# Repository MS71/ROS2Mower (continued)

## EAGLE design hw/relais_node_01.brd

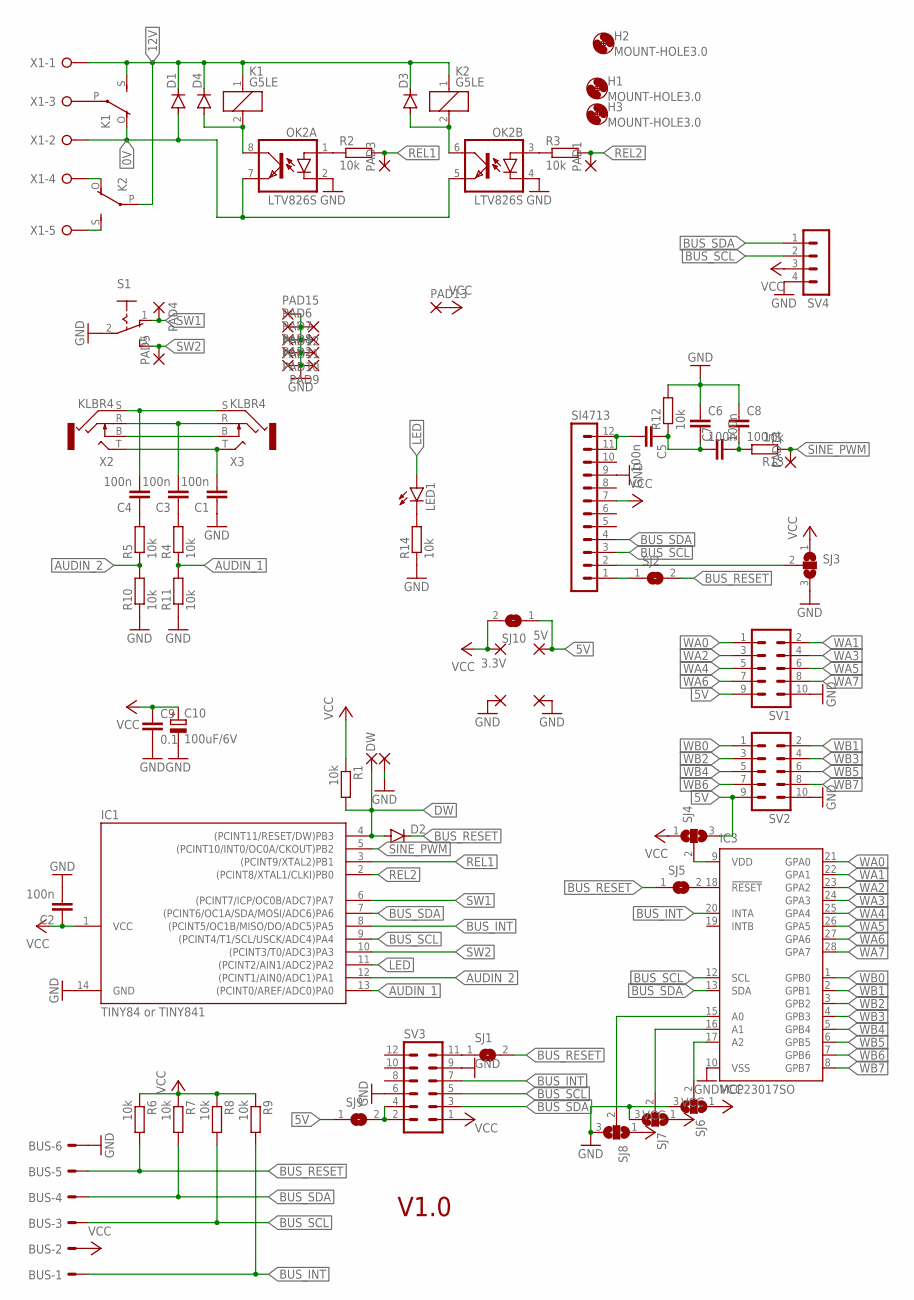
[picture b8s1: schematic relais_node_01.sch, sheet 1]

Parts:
3.3V, 5V: 1,6/0,8
BUS: ML6LE; ML6L
C1, C2, C3, C4, C5, C6, C7, C8: 100n; C0805
C9: 0.1; C0805
C10: 100uF/6V; B/3528-21R
D1: DIODE-MELF-MLL41; MELF-MLL41
D2, D3, D4: DIODE-MINIMELF; MINIMELF
DW: 1,6/0,9
GND_: 1,6/0,9
H1, H2, H3: MOUNT-HOLE3.0; 3,0
IC1: TINY84 or TINY841; SOIC14
IC3: MCP23017SO; SO28W
K1, K2: G5LE
LED1: LED3MM
OK2: LTV826S; DIL8-SMD
PAD1, PAD2, PAD3, PAD4, PAD5, PAD6, PAD7, PAD8, PAD9, PAD10, PAD11, PAD12, PAD13, PAD14, PAD15, PAD16, PAD17: 1,6/0,8
R1, R2, R3, R4, R5, R6, R7, R8, R9, R10, R11, R12, R13, R14: 10k; M0805
S1: 255SB
SI4713: MA12-1
SJ1, SJ2, SJ5, SJ9, SJ10: SJ
SJ3, SJ4, SJ6, SJ7, SJ8: SJ2W; SJ_2
SV1, SV2: ML10
SV3: MA06-2
SV4: MA04-1
X1: W237-05P; W237-5P
X2, X3: KLBR4

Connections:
0V: D1.A, K1.O, OK2.5 (EMIT), OK2.7 (EMIT), X1.2
5V: 5V.1, SJ4.3, SJ9.1, SJ10.1, SV1.9, SV2.9
5VRPI: SJ9.2, SV3.2, SV3.4
12V: D1.C, D3.C, D4.C, K1.1, K1.S, K2.1, K2.P, X1.1
AUDIN_1: IC1.13 ((PCINT0/AREF/ADC0)PA0), R4.1, R11.2
AUDIN_2: IC1.12 ((PCINT1/AIN0/ADC1)PA1), R5.1, R10.2
B: X2.B, X3.B
BUS_INT: BUS.1, IC1.8 ((PCINT5/OC1B/MISO/DO/ADC5)PA5), IC3.20 (INTA), R9.2, SV3.7
BUS_RESET: BUS.5, D2.C, R6.2, SJ1.2, SJ2.2, SJ5.1
BUS_SCL: BUS.3, IC1.9 ((PCINT4/T1/SCL/USCK/ADC4)PA4), IC3.12 (SCL), R8.2, SI4713.3, SV3.5, SV4.2
BUS_SDA: BUS.4, IC1.7 ((PCINT6/OC1A/SDA/MOSI/ADC6)PA6), IC3.13 (SDA), R7.2, SI4713.4, SV3.3, SV4.1
DW: D2.A, DW.1, IC1.4 ((PCINT11/RESET/DW)PB3), R1.2
GND: BUS.6, C1.1, C2.2, C6.1, C8.1, C9.2, C10.-, GND_.1, IC1.14 (GND), IC3.10 (VSS), OK2.2 (C), OK2.4 (C), PAD2.1, PAD6.1, PAD7.1, PAD8.1, PAD9.1, PAD10.1, PAD11.1, PAD12.1, PAD15.1, PAD16.1, PAD17.1, R10.1, R11.1, R12.2, R14.1, S1.2, SI4713.9, SJ3.3, SJ6.3, SJ7.3, SJ8.3, SV1.10, SV2.10, SV3.6, SV3.9, SV4.4
LED: IC1.11 ((PCINT2/AIN1/ADC2)PA2), LED1.A
unnamed: SJ1.1, SV3.11
unnamed: K1.P, X1.3
unnamed: D4.A, K1.2, OK2.8 (COL)
unnamed: D3.A, K2.2, OK2.6 (COL)
unnamed: K2.S, X1.5
unnamed: K2.O, X1.4
unnamed: OK2.1 (A), R2.1
unnamed: OK2.3 (A), R3.1
unnamed: C3.1, R4.2
unnamed: C4.1, R5.2
unnamed: SI4713.1, SJ2.1
unnamed: SI4713.2, SJ3.2
unnamed: LED1.K (C), R14.2
unnamed: IC3.9 (VDD), SJ4.2
unnamed: IC3.18 (!RESET), SJ5.2
unnamed: C5.2, SI4713.11, SI4713.12
unnamed: C5.1, C6.2, C7.1, R12.1
unnamed: C7.2, C8.2, R13.2
unnamed: IC3.17 (A2), SJ6.2
unnamed: IC3.16 (A1), SJ7.2
unnamed: IC3.15 (A0), SJ8.2
R: C3.2, X2.R, X3.R
REL1: IC1.3 ((PCINT9/XTAL2)PB1), PAD3.1, R2.2
REL2: IC1.2 ((PCINT8/XTAL1/CLKI)PB0), PAD1.1, R3.2
S: C4.2, X2.S, X3.S
SINE_PWM: IC1.5 ((PCINT10/INT0/OC0A/CKOUT)PB2), PAD14.1, R13.1
SW1: IC1.6 ((PCINT7/ICP/OC0B/ADC7)PA7), PAD4.1, S1.1 (O)
SW2: IC1.10 ((PCINT3/T0/ADC3)PA3), PAD5.1, S1.3 (S)
T: C1.2, X2.T, X3.T
VCC: 3.3V.1, BUS.2, C2.1, C9.1, C10.+, IC1.1 (VCC), PAD13.1, R1.1, R6.1, R7.1, R8.1, R9.1, SI4713.7, SJ3.1, SJ4.1, SJ6.1, SJ7.1, SJ8.1, SJ10.2, SV3.1, SV4.3
WA0: IC3.21 (GPA0), SV1.1
WA1: IC3.22 (GPA1), SV1.2
WA2: IC3.23 (GPA2), SV1.3
WA3: IC3.24 (GPA3), SV1.4
WA4: IC3.25 (GPA4), SV1.5
WA5: IC3.26 (GPA5), SV1.6
WA6: IC3.27 (GPA6), SV1.7
WA7: IC3.28 (GPA7), SV1.8
WB0: IC3.1 (GPB0), SV2.1
WB1: IC3.2 (GPB1), SV2.2
WB2: IC3.3 (GPB2), SV2.3
WB3: IC3.4 (GPB3), SV2.4
WB4: IC3.5 (GPB4), SV2.5
WB5: IC3.6 (GPB5), SV2.6
WB6: IC3.7 (GPB6), SV2.7
WB7: IC3.8 (GPB7), SV2.8

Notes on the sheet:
V1.0

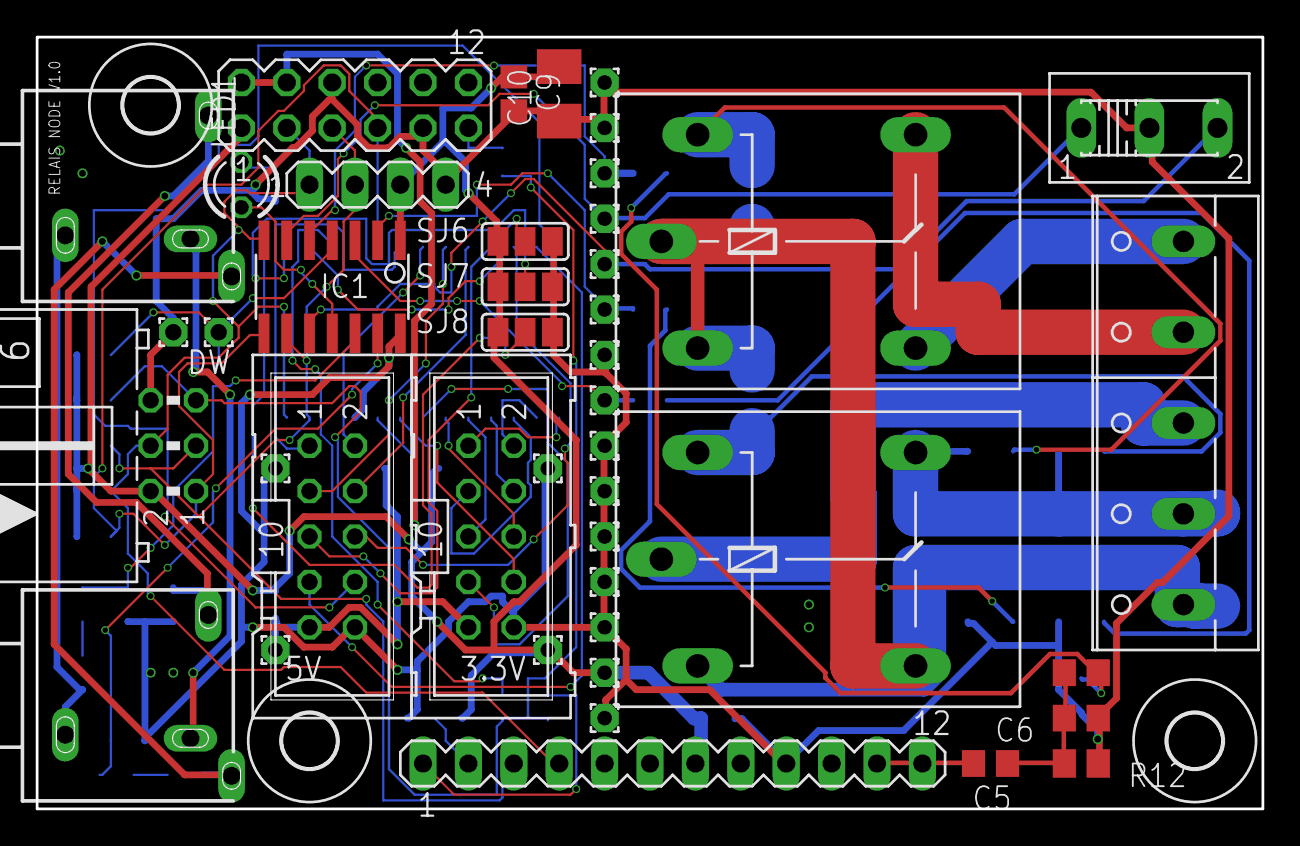
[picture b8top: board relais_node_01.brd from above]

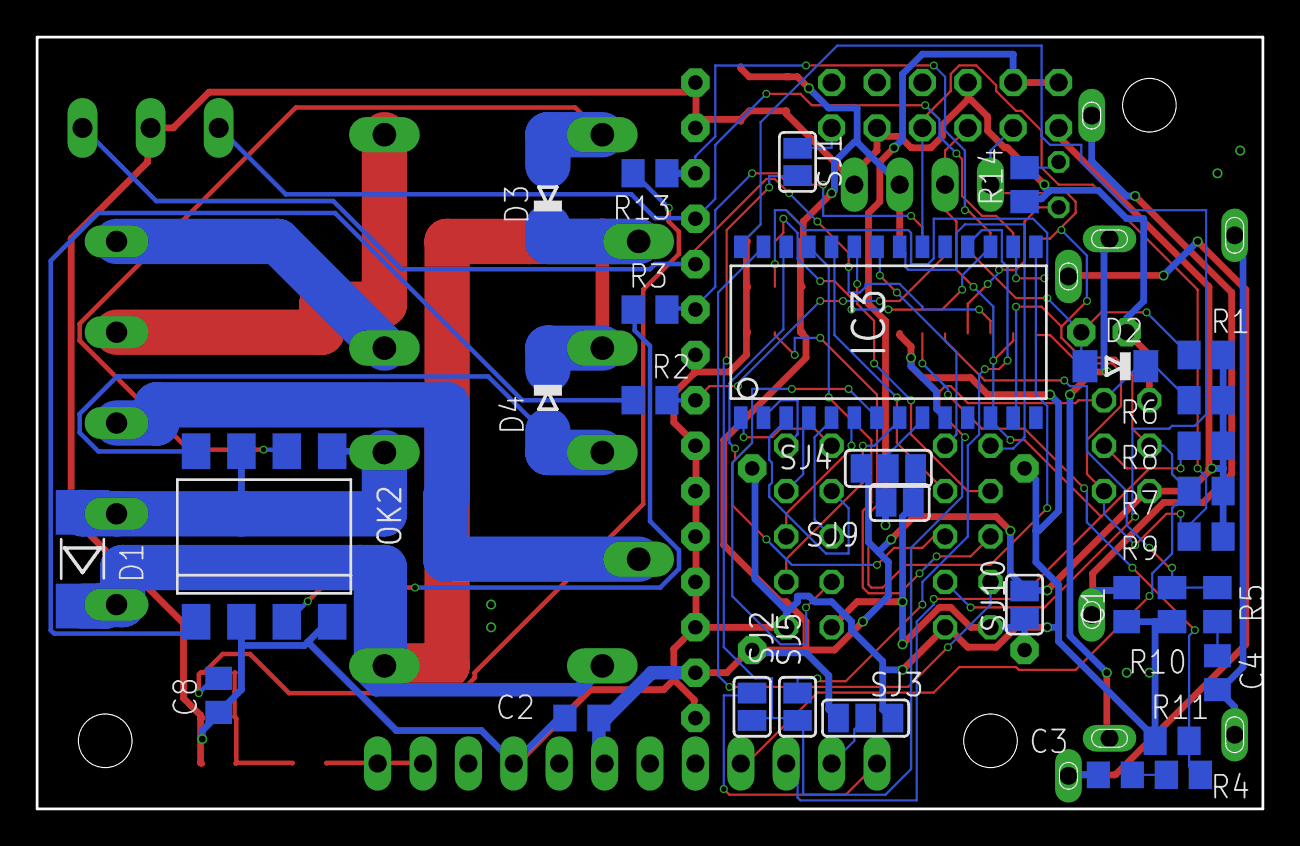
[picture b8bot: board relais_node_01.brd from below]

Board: 2 copper layers, 68.6 x 43.2 mm, 78 parts (31 on the bottom side), 60 nets.

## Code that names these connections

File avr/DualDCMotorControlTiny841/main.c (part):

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#define MOTOR_RPS(_rps_) (int32_t)(((int32_t)_rps_) * MOTOR_GEAR_N)
#define MOTOR_RPM(_rpm_) (int32_t)(MOTOR_RPS(_rpm_) / 60.0)

#define PIN_ENCA	PA0
#define PIN_ENCB	PA1
#define PIN_INA1	PA2
#define PIN_INA2	PA3
#define PIN_INB1	PB1
#define PIN_INB2	PB0
#define PIN_PWMA	PA7
#define PIN_PWMB	PB2
#define PIN_INT  	PA5

//#define DEBUG_INT(_ch_,_v_) if( main_loop_int_pulse == _ch_ ) INTOUT(_v_);
#define DEBUG_INT(_ch_,_v_) 
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
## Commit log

2019-08-13 added
2019-08-15 UBat added
2019-08-15 loopcnt added
2019-08-15 loopcount fixed
2019-08-15 uout, ucharge and usolar added
2020-01-03 gps rtklib added
2020-05-26 esp32 added
2020-06-22 ros2 added
2020-06-27 some improvements on ros2node and motor driver
2020-06-29 support for idf 4.0 added
2020-06-29 i2c problem solved
2020-06-30 default config changed
2020-07-04 motor_node added
2020-07-05 some improvements
2020-07-11 SD card and SPI added
2020-07-19 work in progress
2020-07-19 i2cstress added
2020-07-19 some PCBs added
2020-08-02 some issues fixed
2020-08-02 code merged to avr gcc env
2020-08-02 bug fixed
2020-08-04 pid bug fixed
2020-08-05 improved
2020-08-06 redone
2020-08-09 stabi thread added
2020-08-21 some files updated
2020-08-21 minior monification
2020-08-27 support for tiny841 added
2020-09-03 support for new pcbs added
2020-09-12 rebase to microros app
2020-11-13 current sw
2020-11-26 removed
2021-01-19 changed
